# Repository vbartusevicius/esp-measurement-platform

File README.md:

# ESP Measurement Platform

A 1-DIN rail sensor node and its firmware: tank level (4–20 mA or ultrasonic), pressure or any 0–10 V sensor, Geiger-counter radiation and pulse meters (water, gas, oil, including our optical dial reader), with an OLED, a local web UI, a 230 V relay driven by alert limits, and Home Assistant auto-discovery over MQTT.

<p align="center"><sub>Rendered from the sources: enclosure CAD, the firmware's own OLED drawing code and the web UI (<a href="#regenerating-the-images">how</a>).</sub></p>

> **Status:** hardware v1 is designed and passes DRC, footprint and fit checks, but no board has been built or tested yet. The firmware builds and its unit tests pass in CI.

**Contents:** [Hardware](#hardware-v1) · [Screens](#screens) · [Connecting the sensors](#connecting-the-sensors) · [Alerts and relay](#alerts-and-relay) · [Setup](#setup) · [Home Assistant and MQTT](#home-assistant-and-mqtt) · [Build, flash, test](#build-flash-test)

## Hardware (v1)

| | |
|---|---|
| **Enclosure** | 1 DIN module (18 mm) printed clamshell, or a wall-mount box with the display on its face; terminals on top (sensors) and bottom (power, relay) |
| **Controller** | Seeed XIAO ESP32-C6 on sockets, 4-layer main + UI boards (one breakaway panel) |
| **Power** | 9–30 V DC (24 V nominal), reverse and surge protected, 5 V / 600 mA buck |
| **Inputs** | 10-pole push-in sensor bank: 4–20 mA (120 Ω shunt, 50 mA fuse), 0–10 V, four protected digital lines (ultrasonic, Geiger pulses, meter pulses, I²C/UART), +24 V / +5 V sensor supply |
| **Output** | Relay, COM / NO / NC, 230 VAC up to 2 A, off at power-up |
| **Front** | 0.96" 64×128 OLED, two buttons marked ● (page) and ✕ (reset / WiFi) on their pads, STATUS / NET / SENS LEDs |

Full design, BOM, ordering files, wiring examples, mains-safety notes and open items: **[hardware/releases/v1](hardware/releases/v1/README.md)**.

<details>
<summary><b>Wall-mount box (non-DIN)</b></summary>

The same boards in a 26 × 81 × 70 mm box with screw ears: the main board drops into a tray, the UI board is turned to face the lid beside the terminal legend, and the lid is held by four M3 screws. Files and assembly: [box_enclosure](hardware/releases/v1/box_enclosure) and the [release notes](hardware/releases/v1/README.md).
</details>

<details>
<summary><b>PCBs and accessories</b></summary>

<p align="center">
  
  <br><sub>Optical dial reader: carrier, board, lid and lock ring (separate PCB).</sub>
</p>

<p align="center">
  
  <br><sub>Main board (top, copper) and UI board (top, copper), same scale.</sub>
</p>
<p align="center">
  
  <br><sub>Printable accessories: lid-mount distance sensor pod and the radiation counter duct mount.</sub>
</p>
</details>

<details>
<summary><b>Buttons and LEDs</b></summary>

- **● button** (plain round pad, left): moves to the next sensor (then the DEV, LOG and WIFI pages), or acknowledges a pending alert.
- **✕ button** (pad with an X, right): tap to reboot; hold 5 s to reboot into the WiFi setup portal (settings are kept; hold 5 s again to leave it); hold 15 s for a factory reset. The OLED shows these marks as ● and ✕ in its help lines.
- **STATUS** heartbeat · **NET** green = MQTT, amber = WiFi only, blinking blue = setup portal, blinking red = offline · **SENS** flashes on every sample.
</details>

## Screens

### OLED

Each running sensor has one page: its reading with a 56-point trend and its alert limits as dotted lines, two secondary values, then its own diagnostics: sensor state and terminal signal, plus two rows, the 24 h low/high, or for a pulse meter the time since the last pulse and the 24 h peak flow (its 24 h low is always 0). Device-wide information is shown once instead of on every sensor page: **DEV** has MQTT, WiFi, the relay and which sensor drives it, memory, errors, uptime and the IP; **LOG** the last device events; **WIFI** how to reach the setup portal. Every header shows the WiFi bars, an **M** while the MQTT broker is connected (gone when it is not) and the page number. An alert pops up, naming its sensor, until ● is pressed. If the first board shows the image upside down, set `DISPLAY_ROTATION` to 3 in `lib/Display/Display.cpp`.

### Web UI

Served by the device itself and built per sensor type, following the high-performance HMI guidelines (ISA-101): neutral greys, colour only for abnormal states, and every value shown against its normal and alert range.

| Tank | Pressure | Radiation, alert active |
|:---:|:---:|:---:|
|  |  |  |
| Forecast of when the tank reaches the alert level, from the last 24 h of use | Moving scale with the alert band and the 24 h range | Alert with acknowledge; dose on a log scale with published bands |

<details>
<summary><b>Desktop layout, settings and events</b></summary>

- **Overview:** the relay bar on top (state, the rule in words, e.g. "Turns off while TANK is outside 20–95 %", the last change; a switch in manual mode, a link to the rule in automatic mode). With one sensor, its full view below: headline reading, live or 24 h chart with lowest/average/highest. With several, sub-tabs **All sensors** + one per sensor (marked when it needs attention): *All sensors* lists every alert compactly and shows one equal card per sensor (value, state in words, two key figures, trend against its limits, freshness); a card or an alert's **Details** opens that sensor's tab with only its full view and its alerts. The tab is in the URL (`#overview/<sensor id>`).
- **Events:** device events and the system log on one timeline, newest first and grouped by day, with filters (alerts, relay, sensor faults, network, device, system log; warnings only; per sensor; search), copy and download. The tab shows a badge for alert events not yet seen.
- **Settings:** a collapsible block per sensor type (closed it shows its alert limits, or "Needs attention"), with an on/off switch showing the sensor-bank poles it needs (two sensors on one pole are refused), its parameters (e.g. a Geiger tube list that fills in known values) and its own ON/OFF alert switches; the relay rule and the sensor it follows; device name and MQTT. Alert and relay changes apply immediately; sensor and MQTT changes offer a restart.
- **Device:** status, firmware upload, restart and factory reset.
- Stale data shows its age, and a sensor fault shows "—" with a wiring hint instead of a believable zero.
</details>

<details>
<summary><b>HTTP API</b></summary>

- `GET /api/v1/status` (also pushed as the WebSocket `stats_update` event): device fields (`relay` with its `source` sensor, `events`, `configured`, `errors`, `warnings`, `uptime_s`) and `sensors[]`, one per running sensor: `id`, `name`, `configured`, `screen` (with `kind`: level / pressure / radiation / meter / voltage), `stats[]` (`{key, label, value, numeric}`), `limits`.
- `GET /api/v1/chart?sensor=<id>`: that sensor's 24 h history (`points`, `span_seconds`, `unit`); the first sensor without `sensor`.
- `GET /api/v1/config`: device settings and every sensor type with `enabled`, `inputs` (poles), `prefix`, `topic`, `params` and `limits`. `POST /api/v1/config` takes `sensors` (`"analog_distance,pulse_meter"`) and the sensors' settings under their prefix (`ad.distance_empty`, `pm.limit_high`, ...); unknown sensors or two on one input are refused with 400.
- `POST /api/v1/relay?state=on|off` (409 while an alert rule controls the relay), `POST /api/v1/alert/ack[?sensor=<id>]` (without `sensor`: every pending alert), `POST /api/v1/restart`, `POST /api/v1/reset`, `POST /api/v1/upload` (firmware).
</details>

## Connecting the sensors

Any combination of the five sensors can run at once, since each uses its own poles (they share +5V and GND; use twin ferrules where two wires share a pole). In the web UI under **Settings → Sensors**, switch on each one you have wired up, fill in its settings and save (the device restarts). Each sensor samples and publishes on its own interval.

| Terminal | Pole | Use |
|---|---|---|
| Terminal | Pole | Use |
|---|---|---|
| **J1** (bottom) | 1 GND · 2 VIN | Power in, 9–30 V DC. Use **24 V** for 4–20 mA probes. |
| **Sensor bank** (top, 3.5 mm push-in) | 1 +5V | Sensor supply, 5 V, shared 600 mA budget with the controller |
| | 2 +24V | Sensor supply: the J1 input voltage after the fuse and reverse-polarity diode (about VIN − 0.5 V) |
| | 3 4-20mA | 4–20 mA loop input (120 Ω shunt, 50 mA resettable fuse) |
| | 4 0-10V | Voltage input, 0–10 V |
| | 5 IO1 | Digital: ultrasonic ECHO |
| | 6 IO2 | Digital: ultrasonic TRIG |
| | 7 IO3 | Digital: Geiger counter pulse |
| | 8 IO4 | Digital: meter pulses (dial reader, pulse modules, reed contacts) |
| | 9, 10 GND | Sensor ground |
| **J4** (bottom) | 1 COM · 2 NO · 3 NC | Relay output, 230 VAC ≤ 2 A, fused; see [Alerts and relay](#alerts-and-relay) and the [mains notes](hardware/releases/v1/README.md) |

- **Protection:** IO1–IO4 each have a 330 Ω series resistor, clamp diodes to 3.3 V and a 4.7 kΩ pull-up, so 5 V sensor outputs and open-collector contacts connect directly.
- **Shared poles:** the sensor bank takes 0.14–1.5 mm² wire (strip 8–9 mm; press the grey button to release a wire). There is one +5V and two GND poles, so when two sensors share one, crimp both wires into a twin ferrule (2 × 0.5 mm²).
- **Pole numbers:** they're debossed on the case, as in the table.

### 1. Ultrasonic distance meter (JSN-SR04T / HC-SR04, plugin `ultrasonic_distance`)

| Sensor pin | Terminal |
|---|---|
| VCC (5V) | 1 +5V |
| GND | 9 GND |
| TRIG | 6 IO2 |
| ECHO | 5 IO1 |

- **Settings → Sensors:** switch on Ultrasonic Distance Meter.
- **Empty Distance (cm):** from the sensor face to the surface of an empty tank (the bottom, or the lowest usable level).
- **Full Distance (cm):** from the sensor face to the surface of a full tank. Keep it at least 25 cm for the JSN-SR04T: it can't measure closer than about 20–25 cm (the HC-SR04 manages about 2 cm).
- **Total Volume (L):** optional; adds volume, flow rate and 24 h usage.
- **Mounting:** point the transducer straight down, away from the walls, the inlet and any pipes, which give false short echoes. Condensation on the transducer face does the same.
- **Faults:** if no echo arrives, the UI shows a sensor fault with a wiring hint.

### 2. Analog distance meter (2-wire 4–20 mA level probe, e.g. SWK-LT100, plugin `analog_distance`)

| Probe wire | Terminal |
|---|---|
| Red (+) | 2 +24V |
| Black (−) | 3 4-20mA |
| Shield, if any | 10 GND (at the box end only) |

- **Power:** feed J1 with 24 V. At 20 mA the probe still gets about 20 V; at a 12 V supply it would get only about 8 V, below what most 2-wire transmitters need.
- **Settings → Sensors:** switch on Analog Distance Meter.
- **Sensor Range (m):** the probe's full scale, the depth at 20 mA (e.g. 5 m of water).
- **Empty Reading (cm) / Full Reading (cm):** the depth the probe reports with the tank empty and full. On site, read the probe's depth from the `measured` value (in m) on the MQTT state topic, or from the Overview's *Sensor to surface* tile while **Total Volume** is still empty.
- **Total Volume (L):** optional, as above.
- **Mounting:** hang the probe at the bottom of the tank. The probe cable has a vent tube for the atmospheric reference: don't seal or kink the cable end, and keep it dry.
- **Faults:** below 3.6 mA is a sensor fault (NAMUR NE43), e.g. a broken wire. A short to +24 V trips the 50 mA fuse, which resets about a minute after the fault is gone.

### 3. Pressure sensor, 0–5 V output (plugin `analog_voltage`)

| Sensor wire | Terminal |
|---|---|
| Supply + | 1 +5V (5 V sensors, e.g. ratiometric 0.5–4.5 V) or 2 +24V (sensors rated 9–30 V supply) |
| GND / − | 9 or 10 GND |
| Signal / output | 4 0-10V |

- **Settings → Sensors:** switch on Pressure / 0-10 V Sensor.
- **Settings for a 0–5 V sensor:** Sensor Output at Min (V) = **0**, Sensor Output at Max (V) = **5**, Value at Min = **0**, Value at Max = the sensor's range (e.g. **10**), Unit = **bar** (or psi, kPa…), Decimals and a 4-character Display Title.
- **Settings for a 0.5–4.5 V sensor (the default):** Sensor Output at Min (V) = 0.5, Sensor Output at Max (V) = 4.5.
- **Fault detection:** a 0–5 V sensor can't report a broken wire, because 0 V is a valid reading. A 0.5–4.5 V sensor can: the device reports a fault when its input drops near 0 V. Either type reports a fault when the input is more than 10 % over its range.
- **Accuracy:** a 5 V ratiometric sensor's output scales with the 5 V rail, which is regulated to ±2.5 % and not measured.

### 4. Radiation counter (CAJOE RadiationD-v1.1, plugin `radiation_counter`)

| CAJOE pin (P3 header) | Terminal |
|---|---|
| 5V | 1 +5V |
| GND | 9 or 10 GND |
| VIN (this is the pulse **output**, despite its name) | 7 IO3 |

- **Settings → Sensors:** switch on Radiation Counter Gateway.
- **Geiger tube:** pick the tube printed on the tube (CAJOE boards usually ship with a J305, some with an M4011). This fills in **Tube Factor** (CPM per µSv/h) and **Tube Dead Time**.
  - Both stay editable, and the UI shows when they differ from the preset.
  - Choices: J305, M4011, SBM-20, STS-5, SI-29BG, SBM-19, LND 712, SI-3BG or custom.
  - Published factors vary by about ±20 % between batches (sources in `RadiationCounterPlugin.cpp`), so calibrate against a reference instrument when accuracy matters.
- **Alert Threshold (uSv/h avg):** the 5-minute average that raises the alert (Home Assistant: *Elevated Radiation*).
- **Safety:** the tube runs at about 400 V. Don't touch the tube ends or the high-voltage side of the board while it's powered.
- **Wiring:** keep the pulse wire short.
- **Startup:** the first valid reading takes a minute of counting.
- **Faults:** 5 minutes without a pulse is a fault. Normal background (0.1–0.2 µSv/h) gives about 10–25 CPM on a J305.
- **What it measures:** a glass tube measures ambient gamma radiation, not radon in the air.

### 5. Pulse meter: water, gas, oil (plugin `pulse_meter`)

Counts one pulse per K litres on IO4 from any meter that gives pulses:
- **Optical dial reader:** our own add-on for a mechanical dial, described below.
- **Pulse emitter module:** for example B METERS' IWM-PL3.
- **Gas meter:** a reed contact.
- **Anything else:** any open-collector or 3.3–5 V pulse output.

Settings:
- **Settings → Sensors:** switch on Pulse Meter (water, gas, oil).
- **Medium:** Water, Gas, Oil / fuel or Other. It sets the Home Assistant device class and the entity names, so *Water Meter* or *Gas Meter* (m³, total increasing) can go straight into **Settings → Dashboards → Energy**. *Flow*, *Usage 24h* and *Continuous Flow* are separate entities.
- **Litres per Pulse (K):** the volume per pulse; for the dial reader, the volume of one wheel turn.
- **Meter Reading (m³):** the register on the dial, red pointers included (e.g. `1666.623`).
  - Saving a new value restarts the count from it; leave it unchanged afterwards.
  - The count is saved to flash at most every 10 minutes, so a power cut can lose up to 10 minutes of pulses. Compare with the dial now and then.
- **Min Pulse Gap (ms):** ignores contact noise shorter than this after a counted pulse. 50 ms is far below the pulse period even at a meter's maximum flow.
- **Leak Alert after (h):** warns when something has flowed in every single hour for that long, e.g. a dripping tap or a running cistern. 0 turns it off.
- **Alerts and relay:** the main reading is the flow in L/min, so a high alert of e.g. 30 L/min with *Off during an alert* can close a motorised valve on a burst pipe.

**Optical dial reader (our own add-on).** A reflective IR sensor watches a meter's metal half-disc or pointer through flat glass, so it needs no battery and no pre-equipped meter. It's built for a B METERS GMDM water dial but suits any dial with a reflective wheel and similar hooks.
- **Board:** [`hardware/releases/v1/reader/`](hardware/releases/v1/reader), 31.5 × 18 mm, ordered separately.
- **Housing:** [`accessories/dial_reader/`](hardware/releases/v1/accessories/dial_reader), three printed parts, 16.4 mm tall in total:
  - **Carrier:** holds the board and stands on the glass inside the hooks.
  - **Lid:** screwed onto the carrier, with a grip bar shaped like an arrow pointing at the sensor.
  - **Lock ring:** goes on last, straight down over the closed carrier, and twist-locks onto the dial's three clear hooks. Its six spring fingers press on the lid rim, but the carrier can still be turned to swing the sensor exactly over the wheel.

| Reader terminal (WAGO 2059, solid 0.14–0.34 mm²) | Sensor bank |
|---|---|
| 1 +5V | 1 +5V |
| 2 GND | 9 or 10 GND |
| 3 PULSE | 8 IO4 |

1. **Test print:** print `dial_reader_test_ring.stl` first. Set it on the glass with its tabs beside the hooks and turn it counter-clockwise until it stops; it should not lift off.
2. **Assemble:**
   - Push the board into the carrier, fit the lid with 3 × M2 × 6 self-tapping screws, and push the cable wires (stripped 4–5 mm) into the terminal through the lid's cable hole.
   - Set the carrier on the glass with the arrow towards the wheel, put the ring over it and turn the ring counter-clockwise until it stops.
3. **Point it at the wheel:** open a tap a little and watch the red LED in the ringed window on the lid (it is lit while the sensor sees the disc). Turn the carrier by its grip bar until the LED changes once per wheel turn.
4. **Trimmer (through the hole marked SET):** if the LED stays on or off whatever the carrier position, turn the trimmer until it follows the wheel. Then set it midway between the two points where it stops switching.
5. **Litres per Pulse:** set K to one wheel turn and check it by drawing a known volume (e.g. a 10 L bucket).

**Instead, a B METERS IWM-PL3 pulse module:** white wire → 8 IO4, brown → 9 or 10 GND; insulate the yellow (tamper) and green (backflow) wires. It runs on its own battery.
- **Meter:** it only fits meters pre-equipped for it, the `-I` versions (GMDM-I, GMB-RP-I, GMB-I).
- **Setup:** set its K (1–1000 L) with B METERS' *NFC IWM Config* app and enter the same K here.
- **Not usable:** the RFM-TX1 is a wireless M-Bus radio with no wired output.

## Alerts and relay

Every sensor has its own low and high alert in **Settings → Sensors**, each with an ON/OFF switch and a value in the unit of its main reading (% for tanks, the sensor unit for pressure, µSv/h for radiation, L/min for meters), plus a clear margin (hysteresis). The relay is either **manual** (web UI, MQTT, Home Assistant) or follows the alerts of one sensor chosen under **Settings → Relay output** (**on** or **off during an alert**, e.g. a siren, dry-run protection or closing a valve on a burst pipe); the other sensors only alert. While a rule owns the relay, manual commands are refused, and a sensor fault holds the last state. Changes apply without a restart.

## Setup

1. Flash the firmware (it includes the web UI), see [Build, flash, test](#build-flash-test).
2. On first boot the device opens a WiFi access point `ESP_<ChipID>` (the OLED shows the name). Join it and enter your WiFi; the device restarts.
3. Open the device's IP address (shown on the OLED) and switch on the sensors, fill in their settings and the MQTT broker in **Settings**. An optional **Display name** is what Home Assistant shows.

## Home Assistant and MQTT

Home Assistant discovers one device through the MQTT integration: the entities of every running sensor, plus the heap/RSSI/uptime diagnostics and the relay switch once for the device. Sensor entity ids start with the sensor id (`analog_distance`, `pulse_meter_total`, ...), so sensors side by side never collide.

<details>
<summary><b>Topics and payloads</b></summary>

```
<device_name>/stat/<plugin_id>   one per running sensor: its measurements, at its publish interval
<device_name>/diag               device: heap, RSSI, uptime, version (every 30 s)
<device_name>/availability       LWT: "online" / "offline"
<device_name>/relay              relay state ON / OFF
<device_name>/relay/set          relay command ON / OFF
```

```json
{ "relative": 0.73, "absolute": 1.12, "measured": 1.51, "raw": 1.55, "connected": true,
  "volume": 2340, "flow_rate": 0.42, "usage_24h": 187.3 }
{ "value": 3.4, "voltage": 1.86, "connected": true }
{ "cpm": 42, "dose": 0.34, "dose_avg_5m": 0.29, "counts_total": 183412, "alert": false }
{ "state": "active", "heap": 41520, "rssi": -62, "uptime_s": 3602, "version": "v2026.09.03.2214" }
```

Distance: `volume`, `flow_rate` and `usage_24h` only when **Total Volume** is set. The firmware version is the HA device's `sw_version`.
</details>

## Build, flash, test

Target: `xiao_c6` (USB) / `xiao_c6_ota` (network) for the v1 board, built with the pioarduino platform (Arduino-ESP32 3.x).

```bash
# In Docker, as CI does (PlatformIO Core pinned to 6.1.19)
docker build -f Dockerfile.firmware -t esp-firmware .
docker run --rm -v "$PWD":/project -v esp-pio:/root/.platformio esp-firmware "pio run -e xiao_c6"

pio run -e xiao_c6 -t upload                                  # USB
pio run -e xiao_c6_ota -t upload --upload-port <DEVICE_IP>    # OTA (espota)
pio test -e native                                            # unit tests on the host
```

- **Release files:** every release (and every CI run, as build artifacts) has two images:
  - `firmware.bin`: for **Device → Firmware update** in the web UI; it includes the web UI (`tools/embed_web.py` gzips `data/` into it) and keeps settings. The device refuses the other file here.
  - `firmware-full-usb.bin`: bootloader, partition table and app in one file for an empty or bricked board over USB: `esptool --chip esp32c6 write-flash 0x0 <file>` or the [browser flasher](https://espressif.github.io/esptool-js/). It erases saved settings.
- **Web UI without hardware:** `python3 tools/webui_mock.py`, then open <http://127.0.0.1:8790/?sensor=tank> (scenarios: tank, tank-basic, tank-alarm, pressure, radiation, radiation-high, fault).
- **IDE:** `./setup-ide.sh` generates `compile_commands.json` and `.clangd` for clangd.
- **CI:** builds both targets and runs the tests on every push (`.github/workflows/ci.yml`); releases attach both images.
- Contributor notes (layout, conventions, checks): [AGENTS.md](AGENTS.md).

### Regenerating the images

`python3 tools/readme_images/render.py` rebuilds everything in `doc/images/`: the OLED pages from `lib/Display` through the real U8g2 code, the web UI from `data/` via the mock and headless Chrome, and crops of the hardware renders in `hardware/releases/v1`. Needs Pillow, Chrome and one prior `pio run -e xiao_c6`.

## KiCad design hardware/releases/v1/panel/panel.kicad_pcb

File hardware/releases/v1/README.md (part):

# ESP Measurement Platform Hardware v1 (1-DIN Universal Sensor Node + Plugin Enclosures)

Generated by `python3 hardware/scripts/build.py` from `hardware/circuits/variants/v1/` and `mechanical/scripts/`.
Release gate: KiCad DRC with 0 errors and 0 unrouted connections, pin-for-pin JLCPCB / EasyEDA footprint and
pin-name verification with live stock for every JLC-placed part, and the CadQuery fit tests in `mechanical/tests/`.
Independent pre-order review: `.claude/skills/manufacturing-readiness-review/` (run it before every order).

| View | Render |
| :---: | :---: |
| **1-DIN Universal Sensor Node (Front, Side Legend & Exploded)** |    |
| **1-DIN Isometric & Internal Layout (`main` + `ui`)** |   |
| **Radiation Counter Airduct Assembly** |    |
| **Wall-Mount Box (non-DIN alternative)** |    |
| **Optical Dial Reader (water / gas / oil dials)** |    |
| **Universal Distance Sensor Pod** |    |

### Which files to upload

Every board folder (`main/`, `ui/`, `reader/`) holds the same set; `<b>` is the board name.

| Fab | Bare PCB | Assembly (PCBA) |
|---|---|---|
| **JLCPCB** | `<b>_gerbers.zip` (or `panel/panel_gerbers.zip` for `main` + `ui` in one order) | `<b>_bom_jlc.csv` + `<b>_cpl_jlc.csv`: LCSC numbers, rotations and centres fitted to JLC's own footprints |
| **AISLER** | `<b>_odb.zip` (ODB++) | the same `<b>_odb.zip`: AISLER assembles only from ODB++ or native files, not from Gerbers. Parts auto-assign from the `MPN` field; hand-fit parts carry ODB++'s `.no_pop` flag |
| **Eurocircuits** | `<b>_odb.zip` or `<b>_gerbers.zip` | `<b>_bom.csv` + `<b>_cpl.csv` (they ignore the BOM inside CAD data and ask for a separate one) |
| **PCBWay** and most others | `<b>_gerbers.zip` | `<b>_bom.csv` + `<b>_cpl.csv`; `<b>_ipc2581.zip` (IPC-2581 C with the BOM) where accepted |

- **`<b>_gerbers.zip`:** Gerber X2 copper, mask, paste, silkscreen and outline, Excellon drills with plated and non-plated holes in separate files, the Gerber job file, and `<b>-netlist.ipc` (IPC-D-356) for the electrical test.
- **`<b>_bom.csv`:** grouped by part: Qty, Designator, Value, Manufacturer, MPN, LCSC, Package, SMD/THT, Place (`NO` = hand-fitted after assembly, e.g. the XIAO module) and a description.
- **`<b>_cpl.csv`:** every machine-placed part (hand-fit parts left out) in mm, in the Gerbers' coordinates. Rotations follow KiCad's footprint orientation: check polarised parts in the fab's placement preview, as with JLC.
- **Panel:** only JLCPCB gets the ready-made `main` + `ui` panel; other fabs take the two boards as separate designs.

### Parts for assembling one device yourself

**Where each part goes:** `<board>/<board>_assembly.pdf` (main, ui, reader). It has one page per populated side (the bottom is mirrored, as seen from below). Each page shows every part's outline with its reference and value, a red dot on pin 1 and `*` on hand-fitted parts. Parts of the same value share a colour. The last page lists the values with their colour, quantity, side and references, so you can solder one value at a time. Use it wherever the silkscreen reference had to be hidden. The PDF is vector, so zoom in on the small parts.

`hardware/scripts/parts_orders.py` writes these with every release and looks every LCSC number up live on LCSC: it reports numbers that don't exist, aren't on sale or are short of the quantity. Quantities cover one complete device (`main` + `ui` + `reader`).

| File | Upload to | Map the columns |
|---|---|---|
| `order_lcsc.csv` | [LCSC BOM Tool](https://www.lcsc.com/bom) | **LCSC Part Number** → "LCSC Part #", **Quantity** → "Quantity". Optional: **Manufacturer Part Number** → "Manufacture Part #", **Designators** → "Customer #" / comment. Leave **Value** and **Footprint** unmapped. LCSC raises each line to its minimum order itself (e.g. 100 for 0603 resistors). |
| `order_elsewhere.csv` | Electronics LCSC doesn't sell: pick one shop per line ([Mouser BOM Tool](https://www.mouser.com/bom/), [Digi-Key BOM Manager](https://www.digikey.com/en/mylists/), TME by hand) | Map that shop's column (**Mouser**, **Digi-Key** or **TME**) to its part-number field and **Quantity** to quantity. A line can list numbers at several shops; **Other source** is filled only when no shop number exists (the OLED). Includes the three WAGO terminal blocks: JLCPCB assembles them, but LCSC doesn't sell them. |
| `assembly_parts.csv` | — | Everything off the boards: modules, cables, printed parts and general utility items (foam tape, ...). Utility and printed items appear only here. |

- **One line per LCSC number** in `order_lcsc.csv`, with designators as `board:ref` (`off-board` for the XIAO sockets and the FFC cable).
- **Not in the order files:** printed parts and general utility items (tapes, screws); they are listed in `assembly_parts.csv`.
- **LCSC replacements (2026-10-29):** LCSC had no stock of C14663, C25804 and C28323 and doesn't sell C82401, all four only in JLCPCB's own assembly library. They were replaced in the circuit (`hardware/circuits/common.py`, `blocks/power_24v.py`) by same-package, same-rating parts both LCSC and JLCPCB stock:
  - C14663 → C149620 (YAGEO AC0603KRX7R9BB104, 100 nF 50 V X7R 0603);
  - C25804 → C98220 (YAGEO RC0603FR-0710KL, 10 kΩ 1 % 0603);
  - C28323 → C91185 (YAGEO CC0805KKX7R9BB105, 1 µF 50 V X7R 0805);
  - C82401 → C167838 (CJ FNR4020S220MT, 22 µH 4×4×2.0 mm shielded, 1.1 A Isat, 0.87 A Irms, 455 mΩ; the Sunlord part was 1.05 A / 0.62 A / 455 mΩ).
- **Distributor numbers:** checked by hand on 2026-10-29 and stored in `hardware/scripts/gen_circuits.py` (off-board parts) and `hardware/product/lcsc_unavailable.yaml` (assembled parts LCSC doesn't sell). Mouser and Digi-Key block automated lookups, so only the LCSC numbers are re-checked on each release.

---

## 1. Universal 1-DIN (`18 mm`) Sensor Controller (`main` + `ui`)

| Board | Size | Layers | Thickness | Role | Folder |
|---|---|---|---|---|---|
| **Breakaway Panel (`panel`)** | see `panel/` | 4 | 1.2 mm | Combined `main` + `ui` with mouse-bite tabs (1 PCB + 1 PCBA order) | `panel/` |
| Main (`main`) | 39.8 × 77.4 mm | 4 | 1.2 mm | Vertical board along the left wall (0.2 mm clearance to the 77.8 mm cavity at both ends). 24 V input: 1.1 A PTC, `SS36` 60 V reverse-polarity Schottky, `SMAJ30A` TVS (48.4 V clamp); `SCT2601` 4.5–60 V (65 V abs max) 700 kHz buck → 5.05 V / 600 mA with `SS36` catch diode and 22 µH `FNR4020S220MT` (4×4×2 mm, drop-in for Sunlord `SWPA4020S220MT`); `SS34` Schottky (SMA) into the XIAO ESP32-C6 (on 5 mm female headers); passives 0805 or larger for hand soldering; dedicated 4–20 mA input (50 mA PTC + 120 Ω shunt); 0–10 V input (22 k / 10 k); four protected digital channels (IO1–IO4); all six signal inputs clamped to GND/+3V3 by `BAT54S` (2 µA, 10 pF max); Omron `G6B-2114P-US DC5` relay (1a + 1b joined as a changeover) for **230 VAC loads up to 2 A**, 6 mm creepage + milled slot to the SELV side, 2.5 mm between the relay nets | `main/` |
| UI (`ui`) | 13.8 × 40.5 mm | 4 | 1.2 mm | 0.96" 64×128 SSD1312 OLED (`QG-6428TSWCG02` / `JLX12864OLED-S096W` / `NFP1312-15AY`, 14-pin 0.62 mm solder-tail FPC on `J2`), two Omron `B3U-1000P` switches under C-shaped spring tabs in the front wall, three `WS2812B-MINI-V3J` RGB LEDs with gull-wing legs below them, 0805 passives, 8-pin 0.5 mm FFC (`J1`) to `main J3` | `ui/` |

### Terminal Pinout & Plugin Wiring

Every wire enters parallel to the board, through the top or bottom face of the case.

- **Push-in terminals:** WAGO 2086 3.5 mm SMD, with the release push-buttons in the wire-entry face (300 V / 10 A UL, 0.14–1.5 mm², strip 8–9 mm). Top bank: `J2`, `J5`, `J6`, JLC-assembled. Bottom: `J1` (2086-1202), hand-soldered because JLC has no stock.
- **`J4` (230 V relay):** a Degson `DG127R-5.08-03P` screw terminal (IEC 250 V / 15 A, 0.75–1.5 mm², strip 6–7 mm, M2.5 at 0.4 N·m), JLC-assembled. Its screws are turned through the three holes in the case's right side, under the COM / NO / NC labels.
- **Why not push-in on `J4`:** a 5 mm push-in terminal rated ≥ 250 V would need its release where you can reach it in an 18 mm case. The Kefa KF142R's levers stand 13.7 mm, beyond the case side, where the next DIN module would hold them open; the one fitting Phoenix SPT-SMD part is sold only in reels of 300.

| Terminal | Location | Poles | Function |
|---|---|---|---|
| **Sensor bank: `J2` (2086-1204) + `J5` + `J6` (2086-1203) = 10 poles** | Top | **`1: +5V`** · **`2: +24V`** · **`3: 4-20mA`** · **`4: 0-10V`** · **`5: IO1`** · **`6: IO2`** · **`7: IO3`** · **`8: IO4`** · **`9: GND`** · **`10: GND`** | `1: +5V` (600 mA shared with the controller); `2: +24V` (input after PTC + reverse diode, loop supply); `3: 4-20mA` (`D1/GPIO1/ADC1_CH1`: 50 mA PTC, 120 Ω shunt, 4 mA = 0.48 V, 20 mA = 2.40 V, 24 mA = 2.88 V, 10 k + 100 nF RC); `4: 0-10V` (`D0/GPIO0/ADC1_CH0`, 22 k / 10 k divider, 10 V = 3.125 V); `5: IO1` (`D7/GPIO17`: ECHO / SDA / RX); `6: IO2` (`D6/GPIO16`: TRIG / SCL / TX); `7: IO3` (`D9/GPIO20`: Geiger PULSE); `8: IO4` (`D10/GPIO18`: meter pulse); IO lines: 4.7 k pull-up to 3.3 V, 330 Ω series, `BAT54S` clamp |
| **`J1` (2P)** | Bottom front | **`1: GND`** · **`2: VIN+`** | `9–30 V DC`; 1.1 A PTC, `SS36` reverse protection, `SMAJ30A` surge clamp |
| **`J4` (3P)** | Bottom rear | **`1: COM`** · **`2: NO`** · **`3: NC`** | **230 VAC, 2 A resistive / 1.5 A inductive (cos φ 0.4)**. Omron G6B-2114P: 5 A 250 VAC rated, 3,000 VAC for 1 min and 6 kV impulse between coil and contacts, 11.0 mm tall. Coil pads sit 10.16 mm from the contact pads, with ≥ 6 mm PCB creepage and a milled slot. Fuse the load circuit at ≤ 2 A. The relay is off at power-up and after every reset. |

1. **2-wire 4–20 mA probe (e.g. `SWK-LT100`):** `Red (+)` → pole `2 (+24V)`, `Black (-)` → pole `3 (4-20mA)`. Loop compliance at 20 mA ≈ V<sub>IN</sub> − 0.5 V (diode) − 1.0 V (PTC) − 2.4 V (shunt): ≥ 20 V at 24 V input, ~8 V at 12 V input — check the transmitter's minimum supply.
2. **`0.4–4.5 V` (150 PSI) or `0–10 V` / `2–10 V` sensor:** `+5V`/`+24V` supply, `GND`, signal → pole `4 (0-10V)`. Ratiometric 5 V sensors follow the ±2.5 % buck tolerance (5 V is not measured).
3. **ToF `VL53L1X`/`TOF200C` (I²C) or `A02YYUW` (UART):** `VCC` → pole `1`, `GND` → pole `9`, `SDA/TX` → pole `5 (IO1)`, `SCL/RX` → pole `6 (IO2)`. Keep I²C cables short (≤ 1 m at 100 kHz with the 4.7 k pull-ups).
4. **CAJOE `RadiationD-v1.1`:** `+5V` → pole `1`, `GND` → pole `9`/`10`, `VIN (PULSE)` → pole `7 (IO3)`.
5. **Meter pulse emitter (B METERS `IWM-PL3`, open collector, max 30 V / 100 mA):** `White` (counting contact) → pole `8 (IO4)`, `Brown` (common) → pole `9`/`10 (GND)`; yellow and green unused. The 4.7 k pull-up gives 0.7 mA through the closed contact.
6. **230 VAC load on the relay:** phase from a ≤ 2 A fuse/MCB → `J4.1 (COM)`, load → `J4.2 (NO)` (or `J4.3 (NC)` for normally-on), load return to neutral directly (not through the device). Use 0.75–1.5 mm² wire, strip 11 mm. Control it from Home Assistant (auto-discovered **Relay** switch) or MQTT `<device_name>/relay/set` = `ON`/`OFF`; state on `<device_name>/relay`.

> **Mains safety:** installing this requires a qualified person and a closed distribution board.
> - **Enclosure material:** print the enclosure in a flame-retardant filament (UL94 V-0, e.g. PC-FR or PETG-V0) when J4 carries mains. Plain PETG/ASA is not flame-rated.
> - **Insulation:** the G6B's 3 kVAC / 6 kV coil–contact insulation plus the 8 mm PCB creepage is the barrier between 230 V and the SELV side. Omron does not market the G6B as "reinforced", and nothing here is a certified product.

---

### Printing the 1-DIN case (`enclosure/`, `box_enclosure/`)

- **Process:** sized for powder printing (MJF / SLS, PA12). Every gap inside one printed part is at least 0.6 mm (`MIN_PRINT_GAP`): the DIN latch and its springs, the button C-slots, the UI snap-tongue slots. The 0.2 mm clearances (`FDM_CLEAR`) are only between separately printed parts or between a part and a PCB / terminal body, which cannot fuse.
- **DIN latch:** a 3.6 mm bar on two 11-leg serpentine springs (0.6 mm legs, ≤ 2.5 % strain over the 1.8 mm release travel). Release it with a flat screwdriver in the 3.0 × 1.6 mm hole of the tab below the case.
- **Cover:** six snap clicks (two on the right wall, a pair at each end of the left edge). Its locating lip is bonded to the side wall along its length and notched clear of the snap tongues. Ribs on its left wall back the main board at least every 40 mm, and four base posts support the board's front face, 0.1 mm short, in part-free columns.
- **Front:** no text. The buttons are told apart by their pads: the plain round bump (●) is the page / acknowledge button, the bump with a recessed ✕ (1.5 mm bars, 0.5 mm wide, 0.35 mm deep) is reset / WiFi (tap: reboot; hold 5 s: WiFi setup; hold 15 s: factory reset). The three LEDs are unmarked: STATUS, NET, SENS from left to right. The UI board is held off the front by edge stops beside the LED row.
- **Right side face:** each terminal pole's name is engraved beside it, 3 mm. The sensor bank reads 5V, 24V, mA, 10V, IO1–IO4, GND, GND for poles 1–10, bottom to top along the rail axis. J1 reads GND, VIN under "9-30V", and J4 reads COM, NO, NC under "230V".
- **Terminal access:** `J1`'s push-buttons are in its wire-entry face, so the bottom-wall slot exposes them. `J4`'s screws face the right wall: a 3.0 mm hole over each takes a 2.5 mm flat blade. The screw heads stay 1.5 mm inside the wall, so an IP20 test finger cannot touch them. Wire `J4` before mounting the next DIN module beside it.

## 2. Printable Enclosures & Plugin Accessories

- **`enclosure/`** — 1-DIN (`18 mm`) side-opening clamshell (`base.stl`, `cover.stl`, `assembly.step`), PETG/ASA, 0.2 mm layers.
  - **Assembly:** solder the XIAO sockets, clip all THT solder tails on the back of `main` to ≤ 2.5 mm, slide the populated `main` into the base from the open left side (the terminal blocks run into the top/bottom wall slots, 0.2 mm clearance all round). Stick two strips of 3.0 mm foam tape on the UI board front under the OLED's long edges (on top of the panel's 1.0 mm VHB), snap the UI board into the cover, fit the FFC, then slide the cover on from the left until the four side hooks click. The cover's filler bars close the terminal slots and its side wall has recesses over the THT tails.
  - **Front:** the OLED panel face sits in a 1.0 mm pocket behind the active-area window, pressed forward by the foam; the two buttons are C / mirrored-C spring tabs in the front wall (same design as knx-dali-gateway v3): a 0.7 mm pad on an arm rooted at a shared centre bridge, a rounded 0.6 mm bump on the front for the finger, and a plunger behind ending 0.1 mm above the B3U actuator (no separate parts); LEDs shine through 0.6 mm skins inside baffles.
- **`box_enclosure/`** — wall-mount alternative to the DIN case for the same boards (no PCB changes): `box_base.stl` (back tray with the wall ears) and `box_lid.stl` (the face), 26.4 × 81 × 70.4 mm (93.4 mm wide over the ears), PETG/ASA, 0.2 mm layers, lid face down on the bed.
  - **Layout:** the face is the plane of the DIN case's debossed legend (parallel to `main`) and carries the same terminal legend. Left of it (front view) sits the UI front of the DIN cover (OLED pocket + window, C-shaped button tabs with plungers, LED baffle windows, edge stops, ● / ✕ button pads), rotated 90° to face the lid, ≥ 3 mm from the legend; the UI board's back-side parts are 1.0 mm above the tallest `main` parts (relay, XIAO).
  - **Assembly:** solder the XIAO sockets, clip THT tails to ≤ 2.5 mm, drop the populated `main` straight into the tray (terminal blocks into the top/bottom wall openings, 0.2 mm clearance; the board rests on four posts). Foam-tape the OLED as for the DIN cover, snap the UI board into the lid (four arms hook behind it, blocks locate it within 0.15 mm), fit the same 50 mm FFC (about 32 mm of route with right-angle folds; this fold differs from the DIN case, so check the Type A/B contact side for it too), close the lid (its bars press on the terminal blocks) and fit 4 × M3 × 10 pan-head screws for plastic (2.5 mm pilots, 10 mm deep, in the corner bosses).
  - **Mounting:** one ear on each side at mid-height, Ø 4.0 mm holes 6.5 mm out from the side walls, 83.4 mm apart (3.5 mm wood screws or M3.5). Wires leave through the top (sensors) and bottom (power, relay) faces.
  - **Mains:** the same V-0 filament rule applies when `J4` switches 230 VAC, and the box must be installed where its terminals are not touchable (behind a cover or in a closed cabinet), because the terminal faces are open like on the DIN case.
- **`accessories/radiation_duct/`** — CAJOE box (`cajoe_box_base.stl`, `cajoe_box_cover.stl`) mounted outside a ventilation duct and an in-duct tube bracket (`duct_tube_bracket.stl`) holding the bare J305 tube. See limitations below.
- **`accessories/distance_sensor_pod/`** — lid-mount pod for a `VL53L1X`/`TOF200C` ToF board and/or an `A02YYUW` ultrasonic sensor (`distance_pod_base.stl`, `distance_pod_cover.stl`).
- **`accessories/dial_reader/` + `reader/` (separate PCB order, not on the panel)** — optical dial reader: a pulse emitter for mechanical meters with a reflective (metal) half-disc or pointer under flat glass (water, gas, oil), fitted first to a B METERS GMDM dial in place of an IWM-PL3. Black (IR-opaque) PETG/ASA, 0.2 mm layers.
  - **Board (`reader/`, 31.5 × 18 mm, 4 layers, 1.2 mm, JLC-assembled incl. the THT sensor):** Vishay `TCRT5000` on the back, 0.5 mm above the glass over the wheel (axis 20.5 mm from the dial centre on the GMDM; both spots 4.9 mm from the axis). TI `LMV331` comparator, 80 mV hysteresis, `TC33X` threshold trimmer, red indicator LED (on while the output is low), `B5819W` reverse-polarity diode, open-collector output through 330 Ω. All front parts ≤ 2.7 mm. `J1` WAGO `2059-303` SMD push-in (solid 0.14–0.34 mm², strip 4–5 mm, release with a pin in the round hole): `1 +5V`, `2 GND`, `3 PULSE` → sensor bank poles `1`, `9`/`10`, `8 (IO4)`. About 22 mA at 5 V.
  - **Carrier (`dial_reader_carrier.stl`):** a plain Ø52.0 × 11.8 mm cylinder (the closed carrier with its lid is Ø52.0 all the way up) standing on the glass inside the hooks, which centre it. The PCB sits on rails in a pocket that keeps it square; three U-shaped screw bosses are tied into the wall.
  - **Lock ring (`dial_reader_ring.stl`, skirt down):** Ø62.0 × 15.2 mm, 0.25 mm inside the dial's rotating white ring, which it never needs. It goes on last, straight down over the closed carrier: its tabs and stop ribs reach in only to r 27.25 mm, outside the carrier's r 26.0. The skirt drops into the 1.5 mm gap outside the three clear hooks; three tabs slide under the hooks' 2 mm lips as it turns **22° counter-clockwise** and a rib behind each tab stops the turn. Six spring fingers in its top flange (inner edge r 24.6) press on the lid's outer rim (bump interference 0.9 mm at rest, about 0.6 mm when the tabs bear on the lips). The carrier still turns through 360° under them, so the sensor can be swung exactly over the wheel after the ring is locked.
  - **Lid (`dial_reader_lid.stl`, top down):** Ø52.0 mm, rim pressed by the ring's fingers; four posts press the PCB onto its rails, 3 × M2 × 6 self-tapping screws. Cable hole over the terminal's wire entries, LED and trimmer holes, zip-tie bridge, and an arrow-shaped grip bar (pointing at the sensor) to turn the carrier by.
  - **Fit first:** `dial_reader_test_ring.stl` is the bottom 6 mm of the ring: check the twist lock on the meter before printing the rest. The hook geometry comes from caliper measurements and photos (hook 10.5 × 3.3 × 4 mm, lip 2 mm, notch 1.5 mm, outer face 29.75 mm from the centre, hooks at 180° and ±60° from the wheel).
  - **Setting up:** see the root README, *Pulse meter → optical dial reader*.
---

## 3. Open items before ordering (not verifiable from this repository)

- **Firmware:** `pio run -e xiao_c6` builds for this board; see the root README for the pin map and behaviour. Untested on hardware: OLED rotation (`U8G2_R1`, swap to `U8G2_R3` if upside down), the ADC thresholds of the button ladder, and the WS2812B-MINI-V3J colours.
- **OLED:** pinout verified against the JLX12864OLED-S096W drawing (JLX, 2025-09-17): 1 C2P, 2 C2N, 3 C1P, 4 C1N, 5 VBAT (= VDD), 6 NC, 7 VSS, 8 VDD 3.3 V, 9 RES#, 10 SCL, 11 SDA, 12 IREF (390 k to VSS), 13 VCOMH, 14 VCC; tail 12.0 × 9.3 mm, 14 fingers 0.32 mm at 0.62 mm pitch. Pin 1 is on the right in the front view, which lands on the right (x = 10.93 mm) of `ui J2` after the fold, as placed. The tail-to-pad reach still depends on how tightly the tail is folded; the 2.5 mm pads leave some margin.
- **FFC:** confirm the contact side (Type A/B) of the 50 mm cable against the two connectors' contact sides with a paper mock-up of the fold.
- **WAGO sensor bank:** the 4-pole and two 3-pole blocks are separate, placed butted with 0.15 mm gaps (pole spacing 4.2 mm across each joint). JLCPCB stocks 146 × `2086-1204` and 173 × `2086-1203` (enough for prototypes, not volume). EasyEDA has no footprint for `2086-1203` (C3309626): its land pattern is the 4-pole one's per pole (cited in `hardware/product/pinouts.yaml`). **Check the rotation of `J5`/`J6` in JLCPCB's placement preview:** wire entries face the board edge, like `J2`.
- **Radiation duct:** a glass-walled GM tube measures ambient gamma background; it does not measure radon in the air stream. The flat box base needs a gasket or saddle on a round duct, and the 400 V tube leads in humid duct air can leak.
- **Distance pod:** condensation or salt crust on the ToF window gives short readings; the ultrasonic beam can echo off the tank walls.
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
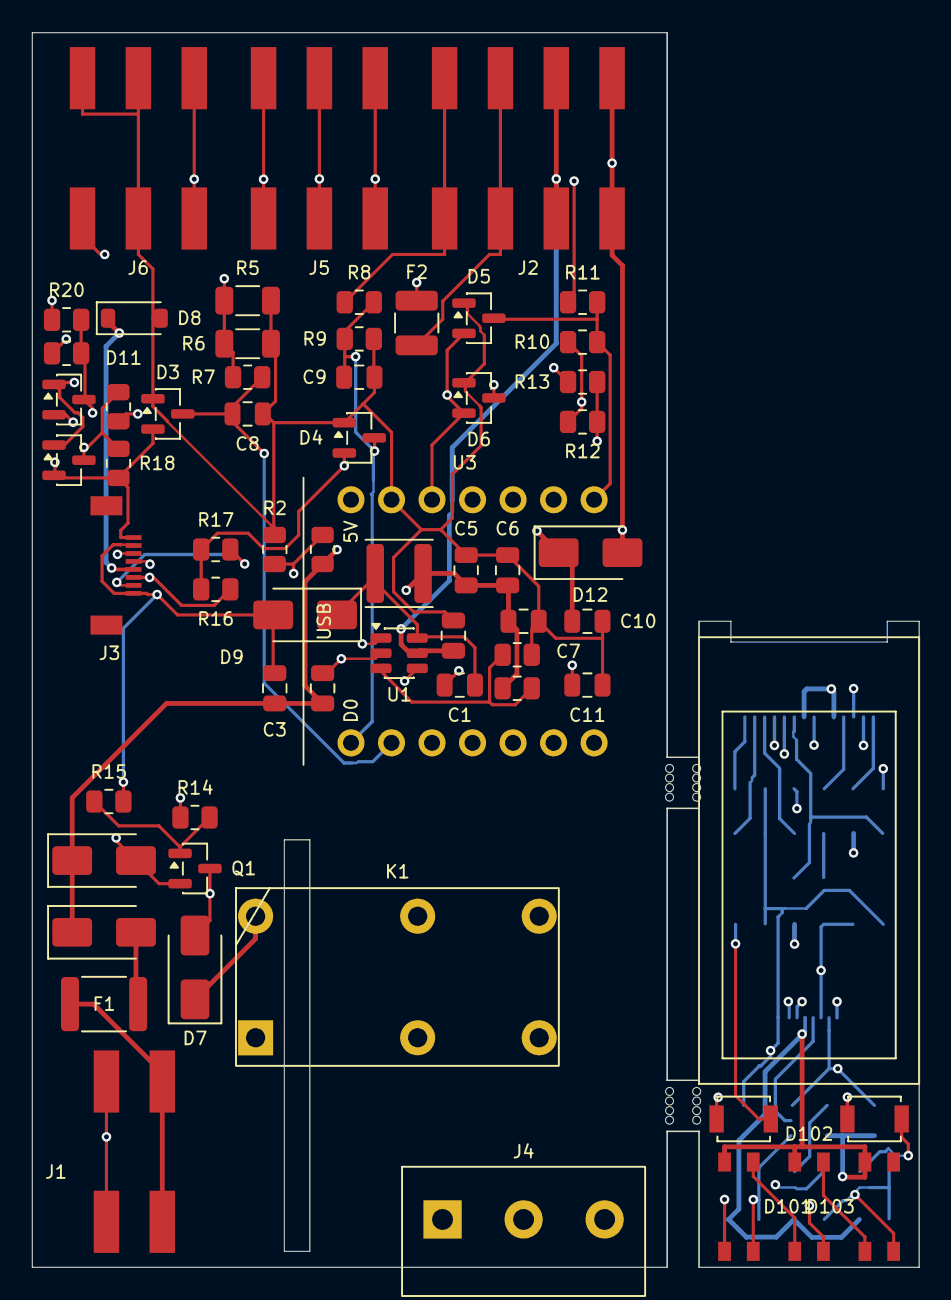
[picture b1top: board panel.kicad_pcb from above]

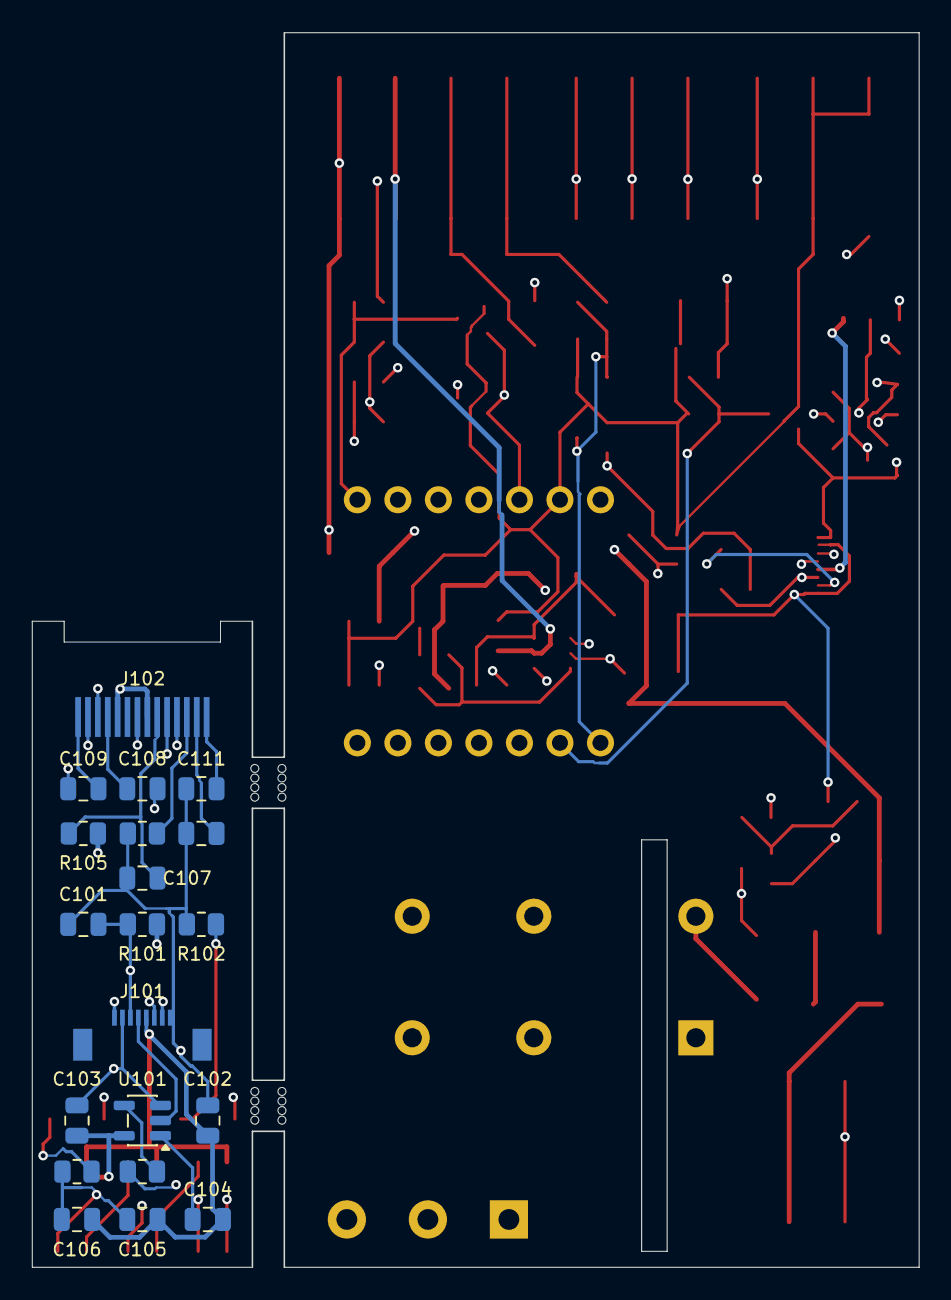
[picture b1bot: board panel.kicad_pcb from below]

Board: 4 copper layers, 55.6 x 77.4 mm, 83 parts (20 on the bottom side), 55 nets.

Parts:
C1, C4, C7, C8, C9, C101, C103, C104, C105, C106, C107: 100n 50V; C_0805_2012Metric
C2, C3: 10u 50V; C_0805_2012Metric
C5, C6: 22u 25V; C_0805_2012Metric
C10, C11: 10u 25V; C_0805_2012Metric
C102, C108, C109, C110, C111: 1u 50V; C_0805_2012Metric
D1: SMAJ30A; D_SMA
D2, D9: SS36; D_SMA
D3, D4, D5, D6, D10, D11: BAT54S; SOT-23
D7, D12: SS34; D_SMA
D8: 5V6; D_SOD-123
D101, D102, D103: WS2812B-MINI-V3J; LED_WS2812B-MINI-V3J
F1: 1.1A; Fuse_1812_4532Metric
F2: 50mA; Fuse_1210_3225Metric
J1: 2086-1202/700-000/997-604; TerminalBlock_WAGO_2086-1202_SMD
J2: 2086-1204/700-000/997-605; TerminalBlock_WAGO_2086-1204_SMD
J3, J101: FPC-05F-8PH20; FPC_Kinghelm_KH-FPC0.5-H1.2SMT-8P
J4: DG127R-5.08-03P; TerminalBlock_Degson_DG127R-5.08-03P
J5, J6: 2086-1203/700-000/997-605; TerminalBlock_WAGO_2086-1203_SMD
J102: OLED; OLED_FPC_14P_P0.62mm_Hotbar
K1: G6B-2114P-US DC5; Relay_1A1B_Omron_G6B-2114P
L1: 22uH; L_Sunlord_SWPA4020S
MOUSE_BITES: DNP
Q1: MMBT3904; SOT-23
R1: 100k; R_0805_2012Metric
R2, R102: 20k; R_0805_2012Metric
R3: 56k; R_0805_2012Metric
R4, R7, R9, R15, R101, R103, R105: 10k; R_0805_2012Metric
R5, R6: 240R; R_1206_3216Metric
R8: 22k; R_0805_2012Metric
R10, R12, R16, R17, R18, R20: 4k7; R_0805_2012Metric
R11, R13, R19, R21, R104: 330R; R_0805_2012Metric
R14: 470R; R_0805_2012Metric
R106: 390k; R_0805_2012Metric
SW101, SW102: B3U-1000P; SW_SPST_B3U-1000P
U1: SCT2601TVBR; TSOT-23-6
U3: XIAO ESP32C6; XIAO_ESP32C6_Header
U101: 74AHCT1G125; SOT-23-5

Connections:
+3V3: C11.1, D3.2, D4.2, D5.2, D6.2, D10.2, D11.2, J3.1, R10.1, R12.1, R16.1, R17.1, R18.1, R20.1, U3.12
+5V: C5.1, C6.1, C7.1, D7.1, D8.1, D12.2, J2.1, J3.5, K1.8, L1.2, R3.1
+5V_XIAO: C10.1, D12.1, U3.14
+24V_LOOP: C2.1, C3.1, C4.1, D1.1, D2.1, J2.2, R1.1, U1.5
BTN_LADDER: J3.3, U3.3
BUCK5_SW: C1.2, D9.1, L1.1, U1.6
GND: C2.2, C3.2, C4.2, C5.2, C6.2, C7.2, C8.2, C9.2, C10.2, C11.2, D1.2, D3.1, D4.1, D5.1, D6.1, D8.2, D9.2, D10.1, D11.1, J1.1, J3.2, J3.8, J6.2, J6.3, Q1.2, R2.2, R4.2, R5.2, R6.2, R9.2, R15.2, U1.2, U3.13
I2C_SCL: J3.7, R17.2, U3.6
I2C_SDA: J3.6, R16.2, U3.5
IO1_MCU: D5.3, R10.2, R11.2, U3.8
IO1_TERM: J5.1, R11.1
IO2_MCU: D6.3, R12.2, R13.2, U3.7
IO2_TERM: J5.2, R13.1
IO3_MCU: D10.3, R18.2, R19.2, U3.10
IO3_TERM: J5.3, R19.1
IO4_MCU: D11.3, R20.2, R21.2, U3.11
IO4_TERM: J6.1, R21.1
LED_DATA: J3.4, U3.4
MA_MCU: C8.1, D3.3, R7.2, U3.2
MA_SHUNT: F2.2, R5.1, R6.1, R7.1
MA_TERM: F2.1, J2.3
unnamed: R1.2, R2.1, U1.4
unnamed: C1.1, U1.1
unnamed: R3.2, R4.1, U1.3
RELAY_BASE: Q1.1, R14.2, R15.1
RELAY_COIL_N: D7.2, K1.1, Q1.3
RELAY_COM: J4.1, K1.3, K1.6
RELAY_MCU: R14.1, U3.9
RELAY_NC: J4.3, K1.5
RELAY_NO: J4.2, K1.4
UI_+3V3: J101.1, J102.5, J102.8, R101.1, R105.1
UI_+5V: C102.1, C103.1, C104.1, C105.1, C106.1, D101.1, D102.1, D103.1, J101.5, U101.5
UI_BTN_LADDER: C101.1, J101.3, R101.2, SW101.1, SW102.1
UI_GND: C101.2, C102.2, C103.2, C104.2, C105.2, C106.2, C107.2, C110.2, C111.2, D101.3, D102.3, D103.3, J101.2, J101.8, J102.7, R102.2, R103.2, R106.2, U101.1, U101.3
UI_I2C_SCL: J101.7, J102.10
UI_I2C_SDA: J101.6, J102.11
UI_LED_CHAIN1: D101.2, D102.4
UI_LED_CHAIN2: D102.2, D103.4
UI_LED_DATA: J101.4, U101.2
UI_N$1: R102.1, SW101.2
UI_N$2: R103.1, SW102.2
UI_N$3: R104.1, U101.4
UI_N$4: D101.4, R104.2
UI_OLED_C1N: C108.2, J102.4
UI_OLED_C1P: C108.1, J102.3
UI_OLED_C2N: C109.2, J102.2
UI_OLED_C2P: C109.1, J102.1
UI_OLED_IREF: J102.12, R106.1
UI_OLED_RES: C107.1, J102.9, R105.2
UI_OLED_VCOMH: C110.1, J102.13
UI_OLED_VOUT: C111.1, J102.14
V0_10_MCU: C9.1, D4.3, R8.2, R9.1, U3.1
V0_10_TERM: J2.4, R8.1
VIN_FUSED: D2.2, F1.2
VIN_RAW: F1.1, J1.2

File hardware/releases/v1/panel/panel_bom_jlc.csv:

Comment,Designator,Footprint,LCSC Part #
1.1A,F1,Fuse_1812_4532Metric,C142747
100k,R1,R_0805_2012Metric,C96346
100n 50V,"C1,C101,C103,C104,C105,C106,C107,C4,C7,C8,C9",C_0805_2012Metric,C49678
10k,"R101,R103,R105,R15,R4,R7,R9",R_0805_2012Metric,C17414
10u 25V,"C10,C11",C_0805_2012Metric,C15850
10u 50V,"C2,C3",C_0805_2012Metric,C440198
1u 50V,"C102,C108,C109,C110,C111",C_0805_2012Metric,C91185
2086-1203/700-000/997-605,"J5,J6",TerminalBlock_WAGO_2086-1203_SMD,C3309626
2086-1204/700-000/997-605,J2,TerminalBlock_WAGO_2086-1204_SMD,C3309718
20k,"R102,R2",R_0805_2012Metric,C4328
22k,R8,R_0805_2012Metric,C17560
22u 25V,"C5,C6",C_0805_2012Metric,C45783
22uH,L1,L_Sunlord_SWPA4020S,C167838
240R,"R5,R6",R_1206_3216Metric,C17961
330R,"R104,R11,R13,R19,R21",R_0805_2012Metric,C17630
390k,R106,R_0805_2012Metric,C17656
470R,R14,R_0805_2012Metric,C17710
4k7,"R10,R12,R16,R17,R18,R20",R_0805_2012Metric,C17673
50mA,F2,Fuse_1210_3225Metric,C118758
56k,R3,R_0805_2012Metric,C17756
5V6,D8,D_SOD-123,C236111
74AHCT1G125,U101,SOT-23-5,C7484
B3U-1000P,"SW101,SW102",SW_SPST_B3U-1000P,C231329
BAT54S,"D10,D11,D3,D4,D5,D6",SOT-23,C47546
DG127R-5.08-03P,J4,TerminalBlock_Degson_DG127R-5.08-03P,C699499
FPC-05F-8PH20,"J101,J3",FPC_Kinghelm_KH-FPC0.5-H1.2SMT-8P,C2856797
G6B-2114P-US DC5,K1,Relay_1A1B_Omron_G6B-2114P,C397217
MMBT3904,Q1,SOT-23,C20526
SCT2601TVBR,U1,TSOT-23-6,C2931912
SMAJ30A,D1,D_SMA,C113965
SS34,"D12,D7",D_SMA,C8678
SS36,"D2,D9",D_SMA,C16015
WS2812B-MINI-V3J,"D101,D102,D103",LED_WS2812B-MINI-V3J,C22371519

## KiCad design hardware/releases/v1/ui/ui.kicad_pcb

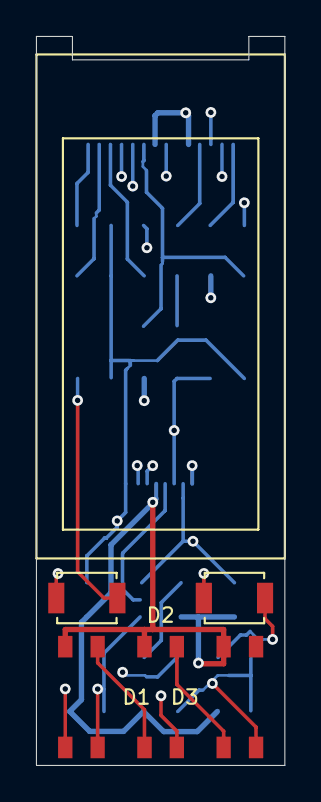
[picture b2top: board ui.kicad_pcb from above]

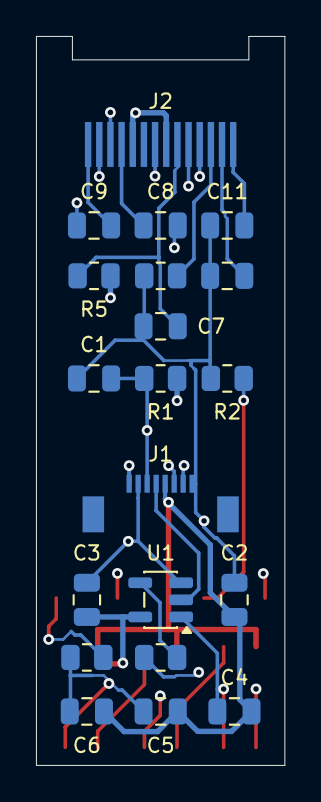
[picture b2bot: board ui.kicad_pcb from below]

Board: 4 copper layers, 13.8 x 40.5 mm, 25 parts (20 on the bottom side), 21 nets.

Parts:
C1, C3, C4, C5, C6, C7: 100n 50V; C_0805_2012Metric
C2, C8, C9, C10, C11: 1u 50V; C_0805_2012Metric
D1, D2, D3: WS2812B-MINI-V3J; LED_WS2812B-MINI-V3J
J1: FPC-05F-8PH20; FPC_Kinghelm_KH-FPC0.5-H1.2SMT-8P
J2: OLED; OLED_FPC_14P_P0.62mm_Hotbar
R1, R3, R5: 10k; R_0805_2012Metric
R2: 20k; R_0805_2012Metric
R4: 330R; R_0805_2012Metric
R6: 390k; R_0805_2012Metric
SW1, SW2: B3U-1000P; SW_SPST_B3U-1000P
U1: 74AHCT1G125; SOT-23-5

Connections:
+3V3: J1.1, J2.5, J2.8, R1.1, R5.1
+5V: C2.1, C3.1, C4.1, C5.1, C6.1, D1.1, D2.1, D3.1, J1.5, U1.5
BTN_LADDER: C1.1, J1.3, R1.2, SW1.1, SW2.1
GND: C1.2, C2.2, C3.2, C4.2, C5.2, C6.2, C7.2, C10.2, C11.2, D1.3, D2.3, D3.3, J1.2, J1.8, J2.7, R2.2, R3.2, R6.2, U1.1, U1.3
I2C_SCL: J1.7, J2.10
I2C_SDA: J1.6, J2.11
LED_CHAIN1: D1.2, D2.4
LED_CHAIN2: D2.2, D3.4
LED_DATA: J1.4, U1.2
unnamed: R2.1, SW1.2
unnamed: R3.1, SW2.2
unnamed: R4.1, U1.4
unnamed: D1.4, R4.2
OLED_C1N: C8.2, J2.4
OLED_C1P: C8.1, J2.3
OLED_C2N: C9.2, J2.2
OLED_C2P: C9.1, J2.1
OLED_IREF: J2.12, R6.1
OLED_RES: C7.1, J2.9, R5.2
OLED_VCOMH: C10.1, J2.13
OLED_VOUT: C11.1, J2.14

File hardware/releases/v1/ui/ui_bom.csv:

Item,Qty,Designator,Value,Manufacturer,MPN,LCSC,Package,Type,Place,Description
1,2,"SW1,SW2",B3U-1000P,Omron,B3U-1000P,C231329,SW_SPST_B3U-1000P,SMD,YES,tap: reboot; hold 5 s: WiFi setup / factory reset
2,1,U1,74AHCT1G125,TI,SN74AHCT1G125DBVR,C7484,SOT-23-5,SMD,YES,"TI SN74AHCT1G125 DBV: 1 OE, 2 A, 3 GND, 4 Y, 5 VCC"
3,3,"R1,R3,R5",10k,UNI-ROYAL,0805W8F1002T5E,C17414,R_0805_2012Metric,SMD,YES,Ladder pull-up; no-button = 3V3
4,1,R2,20k,UNI-ROYAL,0805W8F2002T5E,C4328,R_0805_2012Metric,SMD,YES,RST/WIFI ladder: 3V3*20k/30k=2.2V
5,1,R4,330R,UNI-ROYAL,0805W8F3300T5E,C17630,R_0805_2012Metric,SMD,YES,WS2812B datasheet: series resistor at DIN
6,1,R6,390k,UNI-ROYAL,0805W8F3903T5E,C17656,R_0805_2012Metric,SMD,YES,SSD1312 IREF segment current reference (390k to GND)
7,3,"D1,D2,D3",WS2812B-MINI-V3J,Worldsemi,WS2812B-MINI-V3J,C22371519,LED_WS2812B-MINI-V3J,SMD,YES,"WS2812B-MINI-V3J RGB LED with gull-wing legs, hand-solderable (STATUS)"
8,1,J1,FPC-05F-8PH20,XUNPU,FPC-05F-8PH20,C2856797,FPC_Kinghelm_KH-FPC0.5-H1.2SMT-8P,SMD,YES,8-pin 0.5 mm FFC to main J3
9,5,"C10,C11,C2,C8,C9",1u 50V,YAGEO,CC0805KKX7R9BB105,C91185,C_0805_2012Metric,SMD,YES,5 V entry from the FFC cable
10,6,"C1,C3,C4,C5,C6,C7",100n 50V,YAGEO,CC0805KRX7R9BB104,C49678,C_0805_2012Metric,SMD,YES,Ladder debounce/filter cap
11,1,J2,OLED,Allvision / JLX,QG-6428TSWCG02,,OLED_FPC_14P_P0.62mm_Hotbar,SMD,NO,"Hand-fitted after assembly: 14-pin 0.62 mm pitch (P0.62x13=8.06 mm, 12.0 mm tail, 9.3 mm wide) soldering FPC footprint on the back of the UI board receiving the folded flex tail of the 0.96in 64x128 SSD1312 portrait I2C OLED (QG-6428TSWCG02 / JLX12864OLED-S096W / NFP1312-15AY, 14.0x28.0x1.22 mm)"

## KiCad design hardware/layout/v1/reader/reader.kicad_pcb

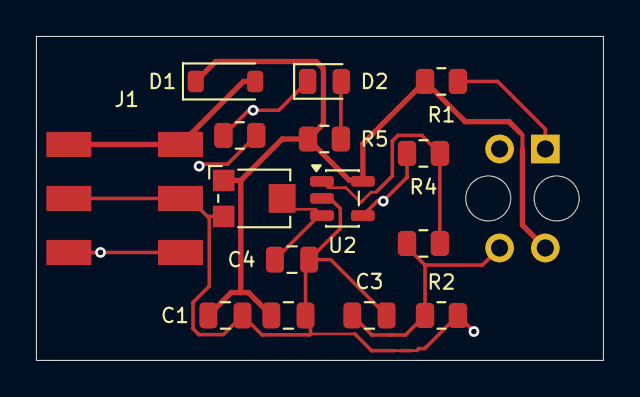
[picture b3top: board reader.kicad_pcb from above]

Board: 4 copper layers, 31.5 x 18.0 mm, 16 parts (1 on the bottom side), 10 nets.

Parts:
C1: 10u 25V; C_0805_2012Metric
C2, C3, C4: 100n 50V; C_0805_2012Metric
D1: B5819W; D_SOD-123
D2: red; LED_0805_2012Metric
J1: 2059-303/998-403; TerminalBlock_WAGO_2059-303_SMD
R1: 220R; R_0805_2012Metric
R2: 4k7; R_0805_2012Metric
R3: 10k; R_0805_2012Metric
R4: 390k; R_0805_2012Metric
R5: 1k; R_0805_2012Metric
R6: 330R; R_0805_2012Metric
RV1: 10k; Potentiometer_Bourns_TC33X_Vertical
U1: TCRT5000; Vishay_TCRT5000_Clips
U2: LMV331; SOT-23-5

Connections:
+5V_IN: D1.2, J1.1
+5V_S: C1.1, C2.1, D1.1, R1.1, R5.1, RV1.1, U1.3, U2.5
CMP_OUT: D2.1, R4.1, R6.1, U2.4
GND: C1.2, C2.2, C3.2, C4.2, J1.2, R2.2, RV1.3, U1.2, U2.2
IR_A: R1.2, U1.1
LED_A: D2.2, R5.2
PULSE: J1.3, R6.2
SENSE: C3.1, R2.1, R3.1, U1.4
SENSE_IN: R3.2, R4.2, U2.1
THRESHOLD: C4.1, RV1.2, U2.3

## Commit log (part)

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2026-04-12 add IDE setup documentation, refactor plugin interface with default methods for display page and sampling interval, move radiation counter interrupts into plugin class
2026-04-12 refactor web UI and display rendering to use generic stats array from plugins, move system info rendering from plugins to Display class, add MQTT connection status to display and web UI
2026-04-12 add github actions
2026-04-14 refactor AnalogDistancePlugin and RadiationCounterPlugin to use HAL abstraction layer, extract calculation logic into separate AnalogDistanceCalculator, AnalogSensorConverter, and RadiationCalculator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
2026-04-14 add GitHub Actions test job with Docker-based native tests, update README with testing documentation, add unsigned int hex constructor to fake String class, fix aggregate test parameters
2026-04-14 start wifi loop early
2026-04-14 feat: add support for unconfigured devices by making plugin selection optional across backend and frontend
2026-04-17 update readme with images
